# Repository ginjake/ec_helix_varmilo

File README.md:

## LICENSE
creative commons non commercial

商用利用したい場合は twitter @sirojake にご相談ください  
please contact me for commercial use.
## developer 
ginjake

商用利用したい場合は twitter @sirojake にご相談ください
please contact me for commercial use.

# ec_helix_varmilo

## 外部の使用ライブラリ
### シンボルライブラリー
phi-kbd-library-master https://github.com/zk-phi/phi-kbd-library  
kbd https://github.com/foostan/kbd  

### フットプリントライブラリー
kbd https://github.com/foostan/kbd  
phi-kbd-library-master https://github.com/zk-phi/phi-kbd-library  
rd https://github.com/KiCad/kicad-footprints/tree/master/Resistor_SMD.pretty  
cs　https://github.com/KiCad/kicad-footprints/tree/master/Capacitor_SMD.pretty

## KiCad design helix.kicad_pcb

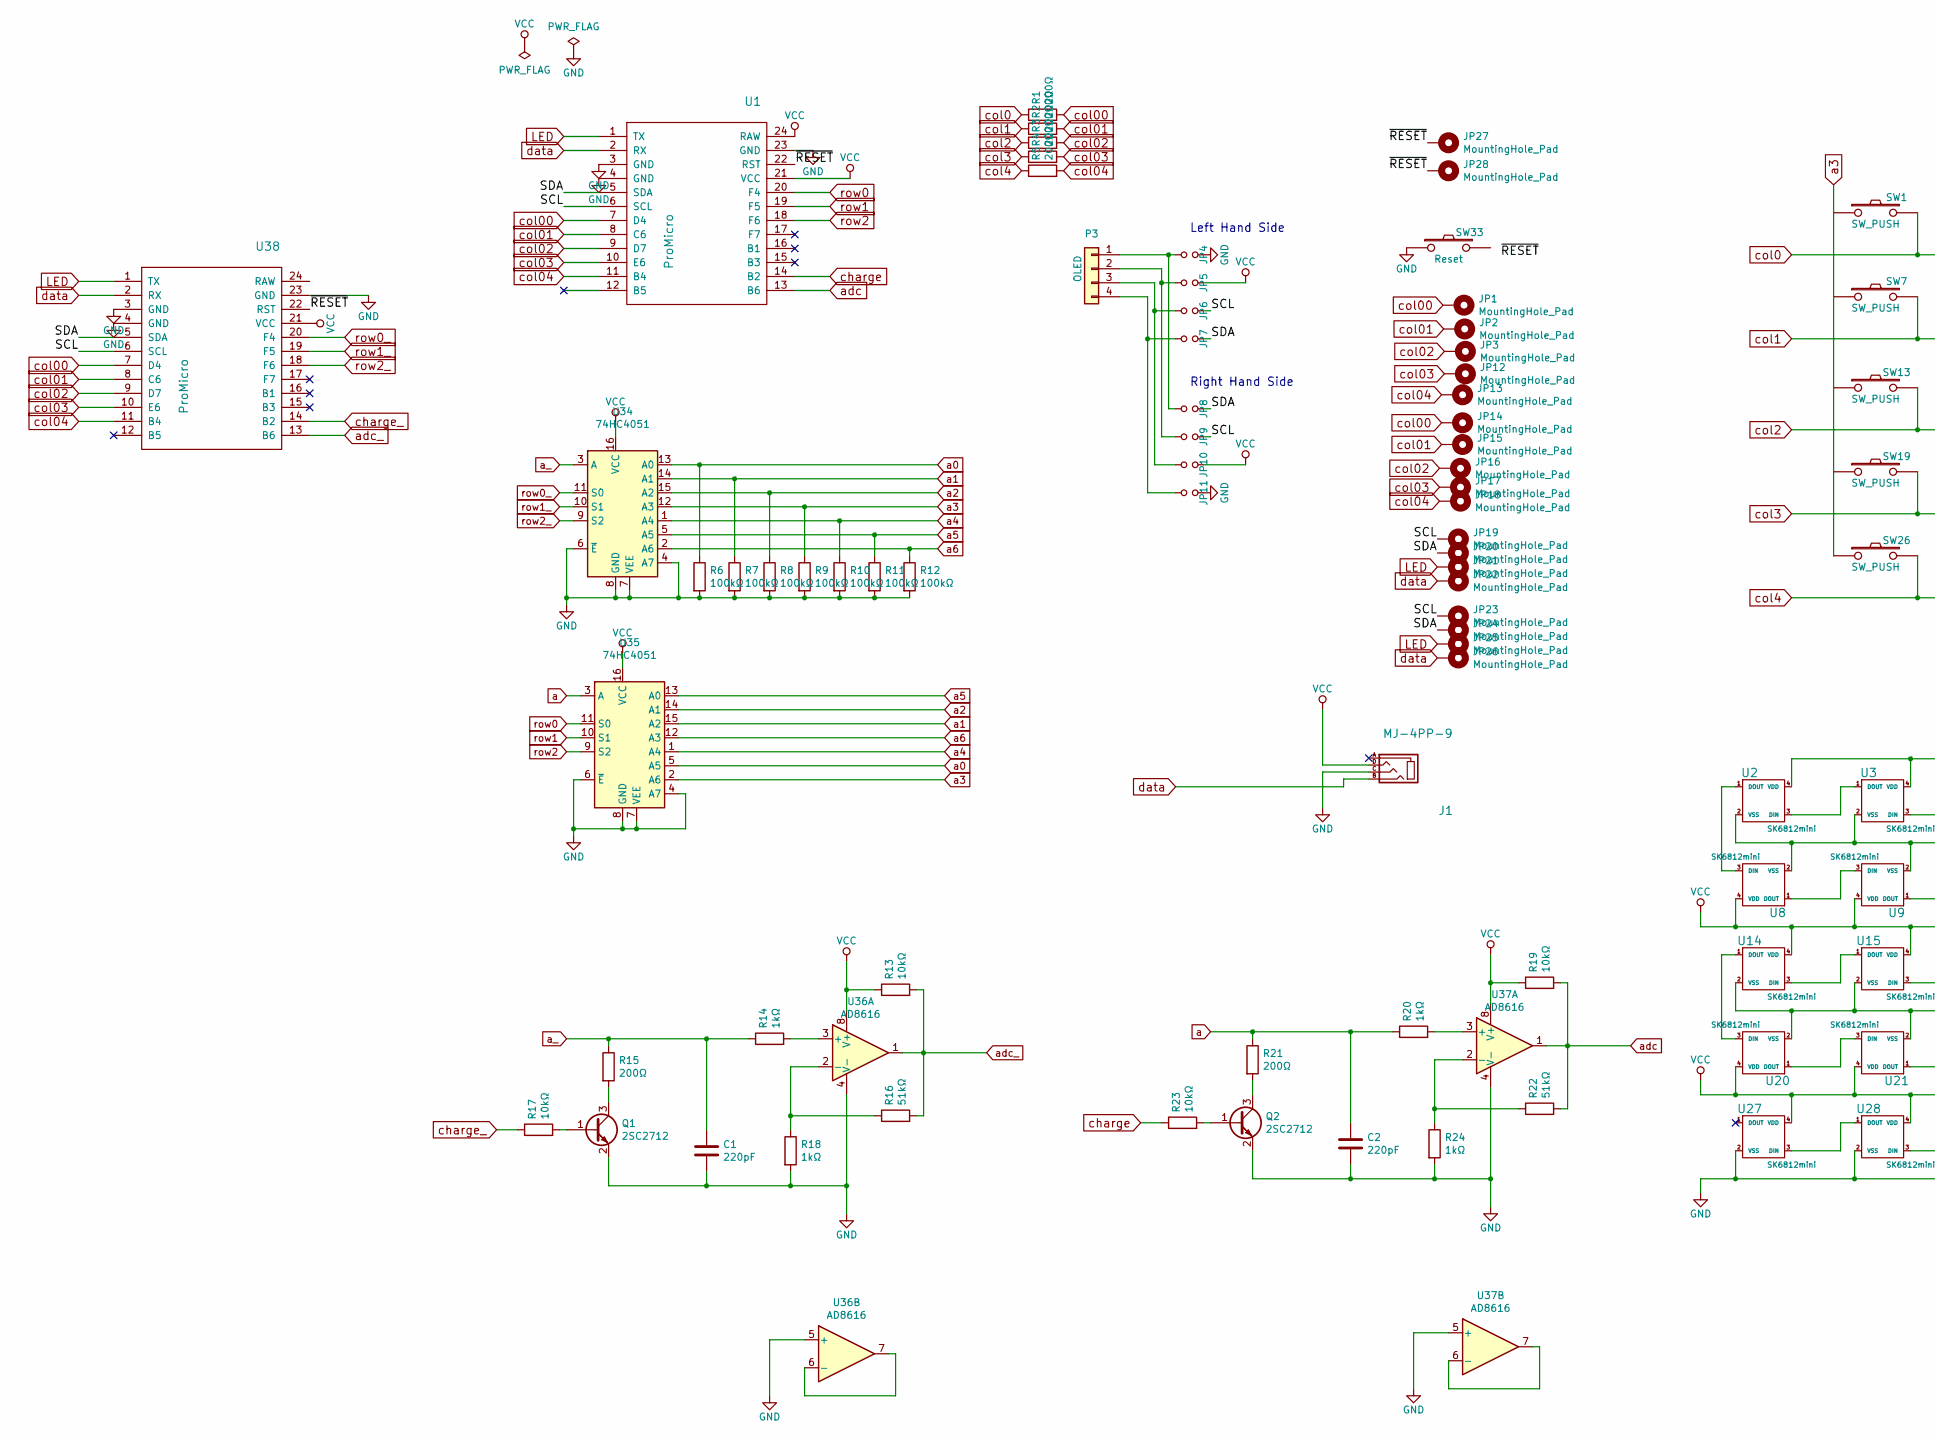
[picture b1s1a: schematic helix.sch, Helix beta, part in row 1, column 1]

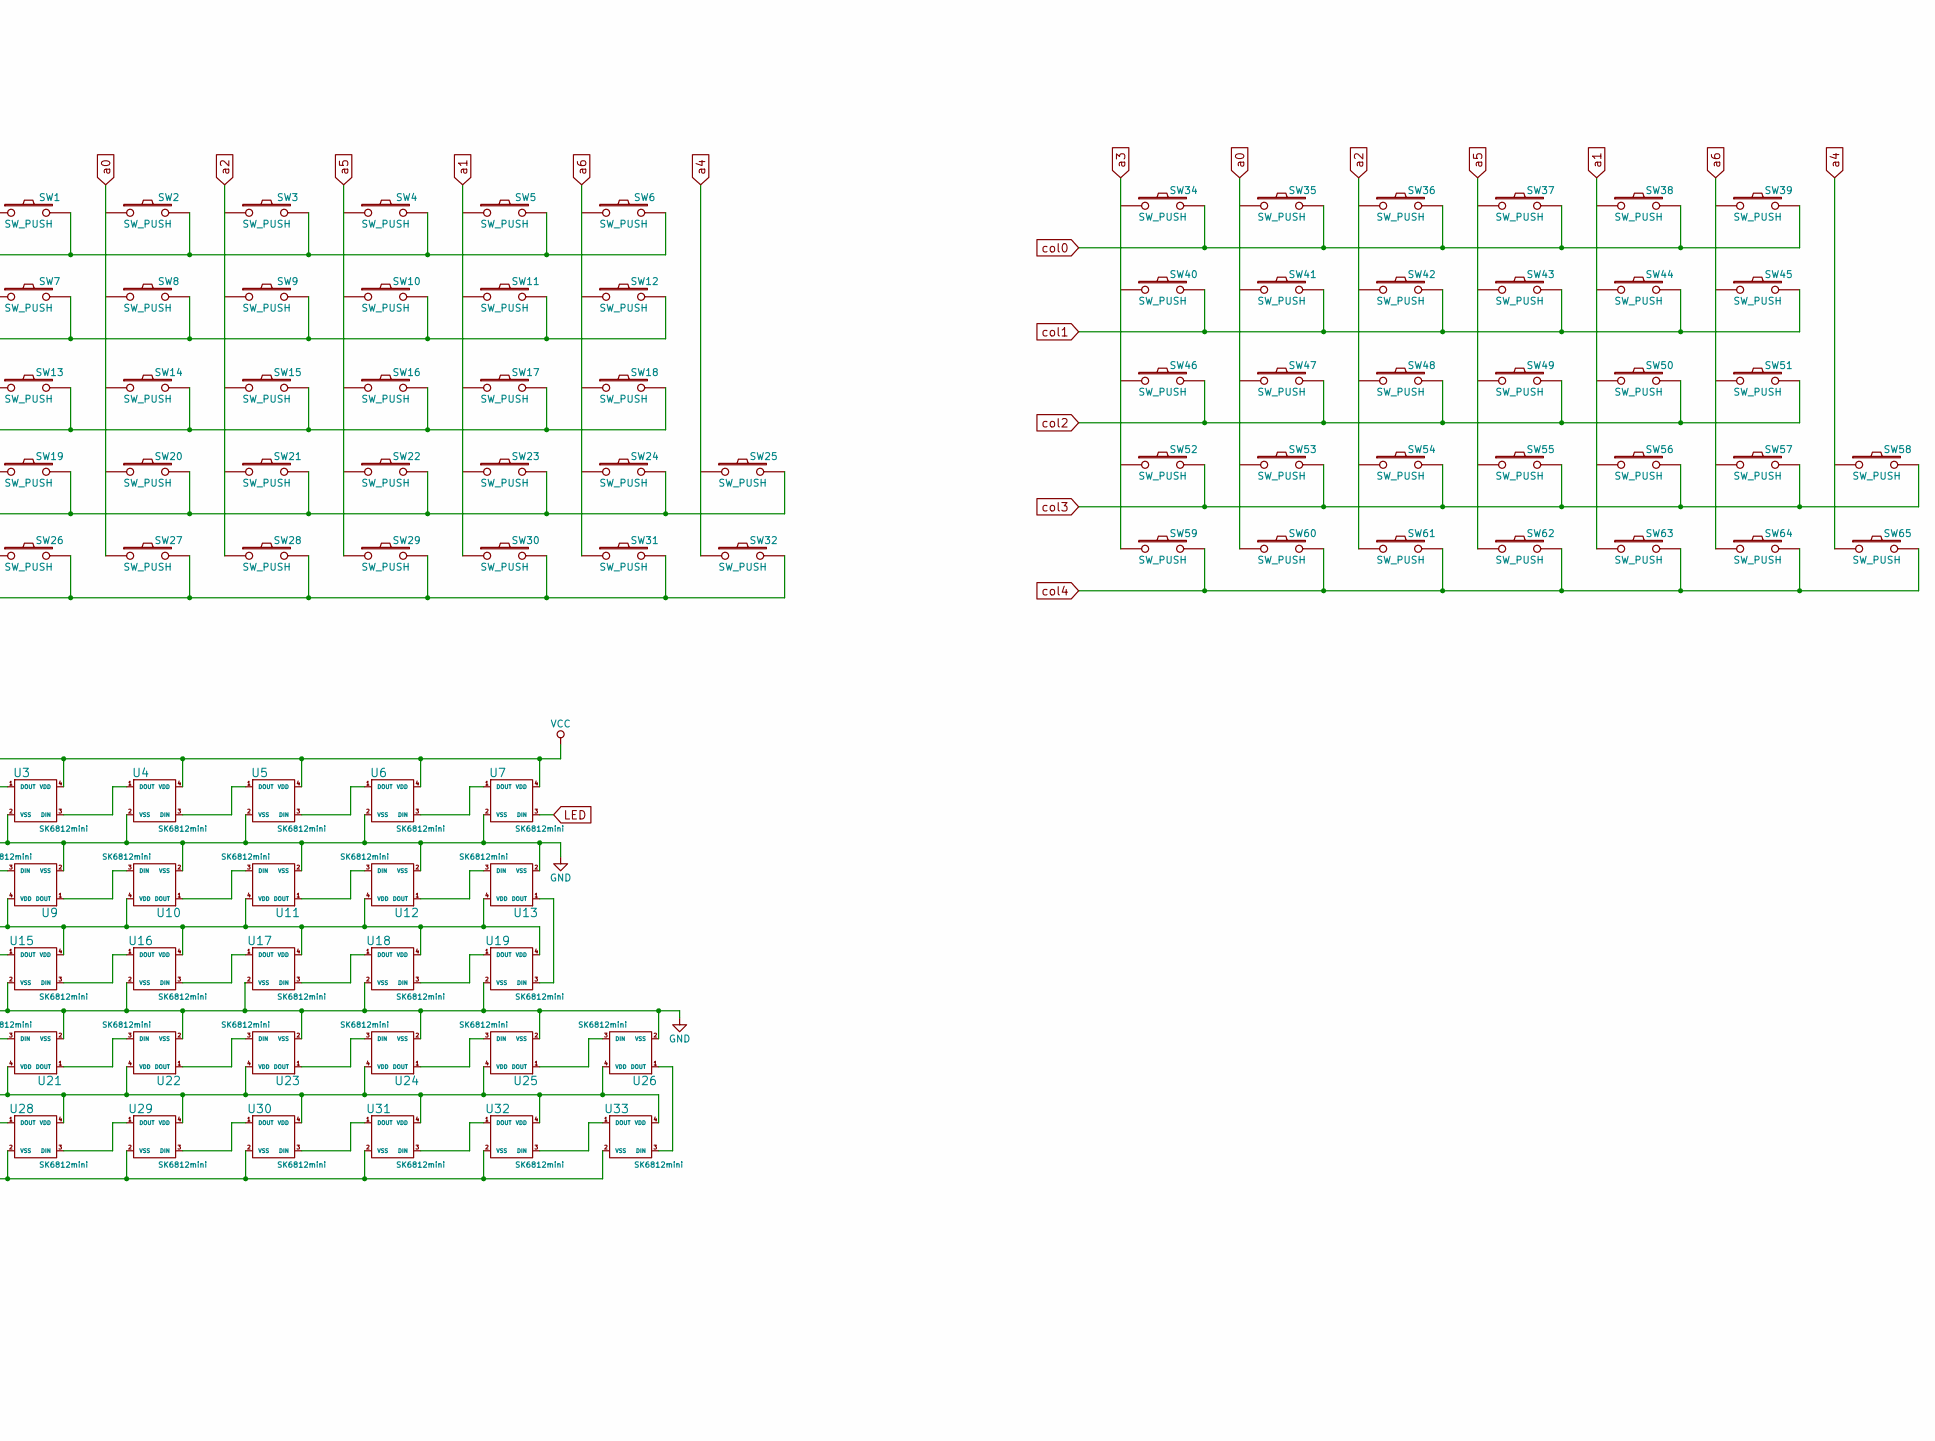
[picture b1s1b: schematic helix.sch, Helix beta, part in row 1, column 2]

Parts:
C1, C2: 220pF; C_0603_1608Metric
J1: MJ-4PP-9
JP1, JP2, JP3, JP12, JP13, JP14, JP15, JP16, JP17, JP18, JP19, JP20, JP21, JP22, JP23, JP24, JP25, JP26, JP27, JP28: MountingHole_Pad; THSmallest
JP4, JP11: GND; Jumper
JP5, JP10: VCC; Jumper
JP6, JP9: SCL; Jumper
JP7, JP8: SDA; Jumper
P3: OLED
Q1, Q2: 2SC2712
R1, R2, R3, R4, R5, R15, R21: 200Ω; R_0603_1608Metric
R6, R7, R8, R9, R10, R11, R12: 100kΩ; R_0603_1608Metric
R13, R17, R19, R23: 10kΩ; R_0603_1608Metric
R14, R18, R20, R24: 1kΩ; R_0603_1608Metric
R16, R22: 51kΩ; R_0603_1608Metric
SW1, SW2, SW3, SW4, SW5, SW6, SW7, SW8, SW9, SW10, SW11, SW12, SW13, SW14, SW15, SW16, SW17, SW18, SW19, SW20, SW21, SW22, SW23, SW24, SW25, SW26, SW27, SW28, SW29, SW30, SW31, SW32, SW34, SW35, SW36, SW37, SW38, SW39, SW40, SW41, SW42, SW43, SW44, SW45, SW46, SW47, SW48, SW49, SW50, SW51, SW52, SW53, SW54, SW55, SW56, SW57, SW58, SW59, SW60, SW61, SW62, SW63, SW64, SW65: SW_PUSH; MX_Hotswap-1.00u-irreversible
SW33: Reset; ResetSW
U1, U38: ProMicro
U2, U3, U4, U5, U6, U7, U8, U9, U10, U11, U12, U13, U14, U15, U16, U17, U18, U19, U20, U21, U22, U23, U24, U25, U26, U27, U28, U29, U30, U31, U32, U33: SK6812mini; SK6812MINI_narrow-irreversible
U34, U35: 74HC4051; SSOP16
U36, U37: AD8616

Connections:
/SCL: JP6.2, JP9.2, JP19.1, JP23.1, U1.6 (SCL), U38.6 (SCL)
/SDA: JP7.2, JP8.2, JP20.1, JP24.1, U1.5 (SDA), U38.5 (SDA)
/~RESET: JP27.1, JP28.1, U1.22 (RST), U38.22 (RST)
GND: C1.2, C2.2, J1.C, JP4.2, JP11.2, Q1.2 (E), Q2.2 (E), R6.2, R7.2, R8.2, R9.2, R10.2, R11.2, R12.2, R18.2, R24.2, SW33.1, U1.3 (GND), U1.4 (GND), U1.23 (GND), U2.2 (VSS), U3.2 (VSS), U4.2 (VSS), U5.2 (VSS), U6.2 (VSS), U7.2 (VSS), U8.2 (VSS), U9.2 (VSS), U10.2 (VSS), U11.2 (VSS), U12.2 (VSS), U13.2 (VSS), U14.2 (VSS), U15.2 (VSS), U16.2 (VSS), U17.2 (VSS), U18.2 (VSS), U19.2 (VSS), U20.2 (VSS), U21.2 (VSS), U22.2 (VSS), U23.2 (VSS), U24.2 (VSS), U25.2 (VSS), U26.2 (VSS), U27.2 (VSS), U28.2 (VSS), U29.2 (VSS), U30.2 (VSS), U31.2 (VSS), U32.2 (VSS), U33.2 (VSS), U34.4 (A7), U34.6 (~E), U34.7 (VEE), U34.8 (GND), U35.4 (A7), U35.6 (~E), U35.7 (VEE), U35.8 (GND), U36.4 (V-), U36.5 (+), U37.4 (V-), U37.5 (+), U38.3 (GND), U38.4 (GND), U38.23 (GND)
LED: JP21.1, JP25.1, U1.1 (TX), U7.3 (DIN), U38.1 (TX)
unnamed: JP4.1, JP8.1, P3.1
unnamed: JP5.1, JP9.1, P3.2
unnamed: JP6.1, JP10.1, P3.3
unnamed: JP7.1, JP11.1, P3.4
unnamed: Q1.1 (B), R17.2
unnamed: Q1.3 (C), R15.2
unnamed: Q2.1 (B), R23.2
unnamed: Q2.3 (C), R21.2
unnamed: R14.2, U36.3 (+)
unnamed: R16.1, R18.1, U36.2 (-)
unnamed: R20.2, U37.3 (+)
unnamed: R22.1, R24.1, U37.2 (-)
unnamed: U2.1 (DOUT), U8.3 (DIN)
unnamed: U2.3 (DIN), U3.1 (DOUT)
unnamed: U3.3 (DIN), U4.1 (DOUT)
unnamed: U4.3 (DIN), U5.1 (DOUT)
unnamed: U5.3 (DIN), U6.1 (DOUT)
unnamed: U6.3 (DIN), U7.1 (DOUT)
unnamed: U8.1 (DOUT), U9.3 (DIN)
unnamed: U10.1 (DOUT), U11.3 (DIN)
unnamed: U9.1 (DOUT), U10.3 (DIN)
unnamed: U11.1 (DOUT), U12.3 (DIN)
unnamed: U12.1 (DOUT), U13.3 (DIN)
unnamed: U13.1 (DOUT), U19.3 (DIN)
unnamed: U14.1 (DOUT), U20.3 (DIN)
unnamed: U14.3 (DIN), U15.1 (DOUT)
unnamed: U15.3 (DIN), U16.1 (DOUT)
unnamed: U16.3 (DIN), U17.1 (DOUT)
unnamed: U17.3 (DIN), U18.1 (DOUT)
unnamed: U18.3 (DIN), U19.1 (DOUT)
unnamed: U20.1 (DOUT), U21.3 (DIN)
unnamed: U21.1 (DOUT), U22.3 (DIN)
unnamed: U22.1 (DOUT), U23.3 (DIN)
unnamed: U23.1 (DOUT), U24.3 (DIN)
unnamed: U24.1 (DOUT), U25.3 (DIN)
unnamed: U25.1 (DOUT), U26.3 (DIN)
unnamed: U26.1 (DOUT), U33.3 (DIN)
unnamed: U27.3 (DIN), U28.1 (DOUT)
unnamed: U28.3 (DIN), U29.1 (DOUT)
unnamed: U29.3 (DIN), U30.1 (DOUT)
unnamed: U30.3 (DIN), U31.1 (DOUT)
unnamed: U31.3 (DIN), U32.1 (DOUT)
unnamed: U32.3 (DIN), U33.1 (DOUT)
unnamed: U36.6 (-), U36.7
unnamed: U37.6 (-), U37.7
VCC: J1.D, JP5.2, JP10.2, R13.1, R19.1, U1.21 (VCC), U1.24 (RAW), U2.4 (VDD), U3.4 (VDD), U4.4 (VDD), U5.4 (VDD), U6.4 (VDD), U7.4 (VDD), U8.4 (VDD), U9.4 (VDD), U10.4 (VDD), U11.4 (VDD), U12.4 (VDD), U13.4 (VDD), U14.4 (VDD), U15.4 (VDD), U16.4 (VDD), U17.4 (VDD), U18.4 (VDD), U19.4 (VDD), U20.4 (VDD), U21.4 (VDD), U22.4 (VDD), U23.4 (VDD), U24.4 (VDD), U25.4 (VDD), U26.4 (VDD), U27.4 (VDD), U28.4 (VDD), U29.4 (VDD), U30.4 (VDD), U31.4 (VDD), U32.4 (VDD), U33.4 (VDD), U34.16 (VCC), U35.16 (VCC), U36.8 (V+), U37.8 (V+), U38.21 (VCC)
a: C2.1, R20.1, R21.1, U35.3 (A)
a0: R6.1, SW27.1, SW60.1, U34.13 (A0), U35.5 (A5)
a1: R7.1, SW30.1, SW63.1, U34.14 (A1), U35.15 (A2)
a2: R8.1, SW28.1, SW61.1, U34.15 (A2), U35.14 (A1)
a3: R9.1, SW26.1, SW59.1, U34.12 (A3), U35.2 (A6)
a4: R10.1, SW32.1, SW65.1, U34.1 (A4), U35.1 (A4)
a5: R11.1, SW29.1, SW62.1, U34.5 (A5), U35.13 (A0)
a6: R12.1, SW31.1, SW64.1, U34.2 (A6), U35.12 (A3)
a_: C1.1, R14.1, R15.1, U34.3 (A)
adc: R19.2, R22.2, U1.13 (B6), U37.1
adc_: R13.2, R16.2, U36.1, U38.13 (B6)
charge: R23.1, U1.14 (B2)
charge_: R17.1, U38.14 (B2)
col00: JP1.1, JP14.1, R1.2, U1.7 (D4), U38.7 (D4)
col0: R1.1, SW1.2, SW2.2, SW3.2, SW4.2, SW5.2, SW6.2, SW34.2, SW35.2, SW36.2, SW37.2, SW38.2, SW39.2
col01: JP2.1, JP15.1, R2.2, U1.8 (C6), U38.8 (C6)
col1: R2.1, SW7.2, SW8.2, SW9.2, SW10.2, SW11.2, SW12.2, SW40.2, SW41.2, SW42.2, SW43.2, SW44.2, SW45.2
col02: JP3.1, JP16.1, R3.2, U1.9 (D7), U38.9 (D7)
col2: R3.1, SW13.2, SW14.2, SW15.2, SW16.2, SW17.2, SW18.2, SW46.2, SW47.2, SW48.2, SW49.2, SW50.2, SW51.2
col03: JP12.1, JP17.1, R4.2, U1.10 (E6), U38.10 (E6)
col3: R4.1, SW19.2, SW20.2, SW21.2, SW22.2, SW23.2, SW24.2, SW25.2, SW52.2, SW53.2, SW54.2, SW55.2, SW56.2, SW57.2, SW58.2
col04: JP13.1, JP18.1, R5.2, U1.11 (B4), U38.11 (B4)
col4: R5.1, SW26.2, SW27.2, SW28.2, SW29.2, SW30.2, SW31.2, SW32.2, SW59.2, SW60.2, SW61.2, SW62.2, SW63.2, SW64.2, SW65.2
data: J1.B, JP22.1, JP26.1, U1.2 (RX), U38.2 (RX)
row0: U1.20 (F4), U35.11 (S0)
row0_: U34.11 (S0), U38.20 (F4)
row1: U1.19 (F5), U35.10 (S1)
row1_: U34.10 (S1), U38.19 (F5)
row2: U1.18 (F6), U35.9 (S2)
row2_: U34.9 (S2), U38.18 (F6)

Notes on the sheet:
Left Hand Side
Right Hand Side

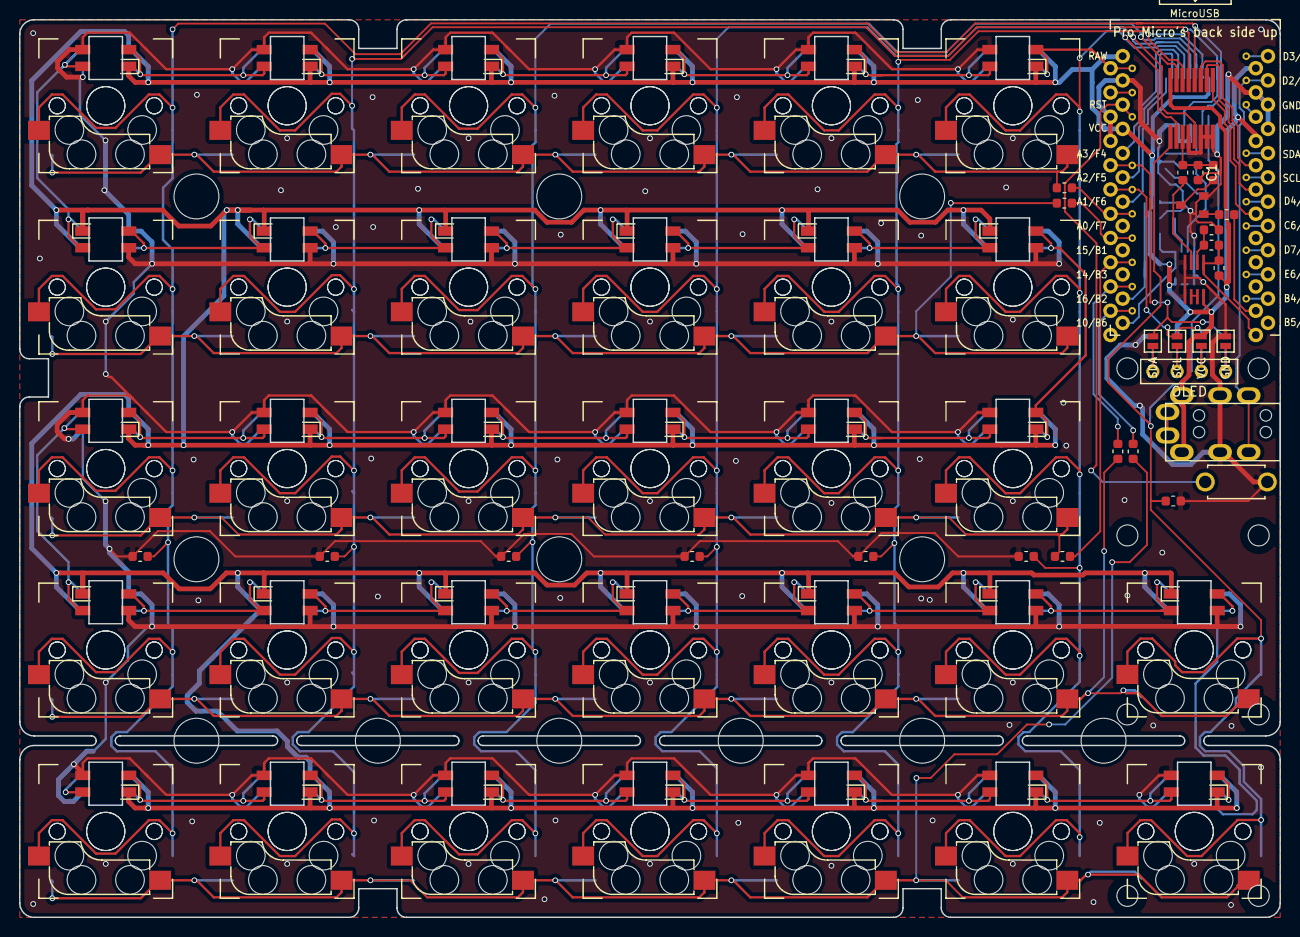
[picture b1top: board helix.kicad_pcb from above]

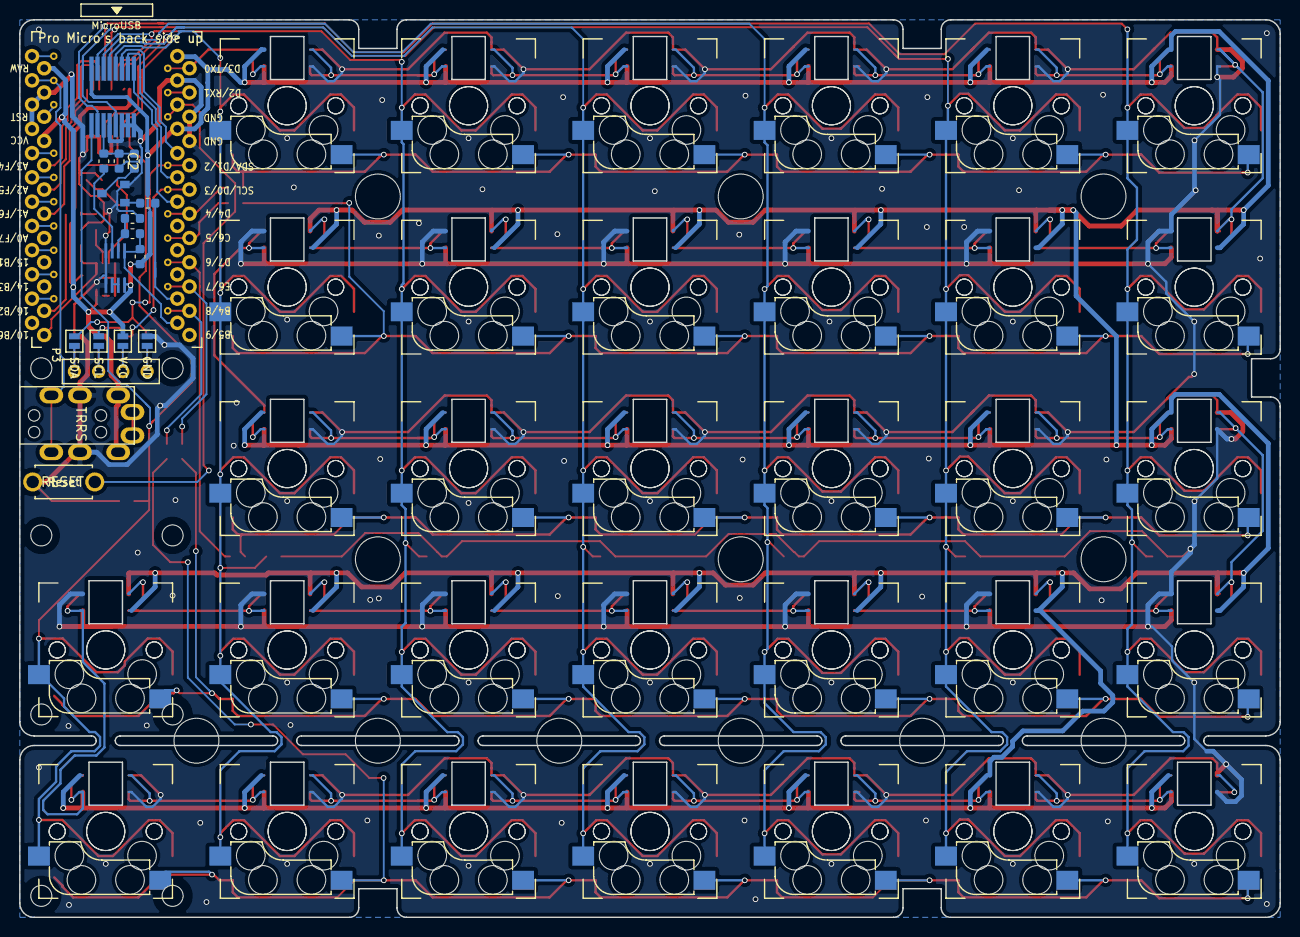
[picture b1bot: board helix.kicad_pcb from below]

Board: 2 copper layers, 132.0 x 94.0 mm, 181 parts (47 on the bottom side), 81 nets.

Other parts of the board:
HOLE_3M, HOLE_3M#2, HOLE_3M#3, HOLE_3M#4, HOLE_3M#5, HOLE_3M#6, HOLE_3M#7, HOLE_3M#8, HOLE_3M#9, HOLE_3M#10, HOLE_3M#11, HOLE_3M#12: VAL**; HOLE_M2_TH
HOLE_M2, HOLE_M2#2, HOLE_M2#3, HOLE_M2#4, HOLE_M2#5, HOLE_M2#6, HOLE_M2#7, HOLE_M2#8: VAL**; HOLE_M2

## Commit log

2020-06-20 コミット
